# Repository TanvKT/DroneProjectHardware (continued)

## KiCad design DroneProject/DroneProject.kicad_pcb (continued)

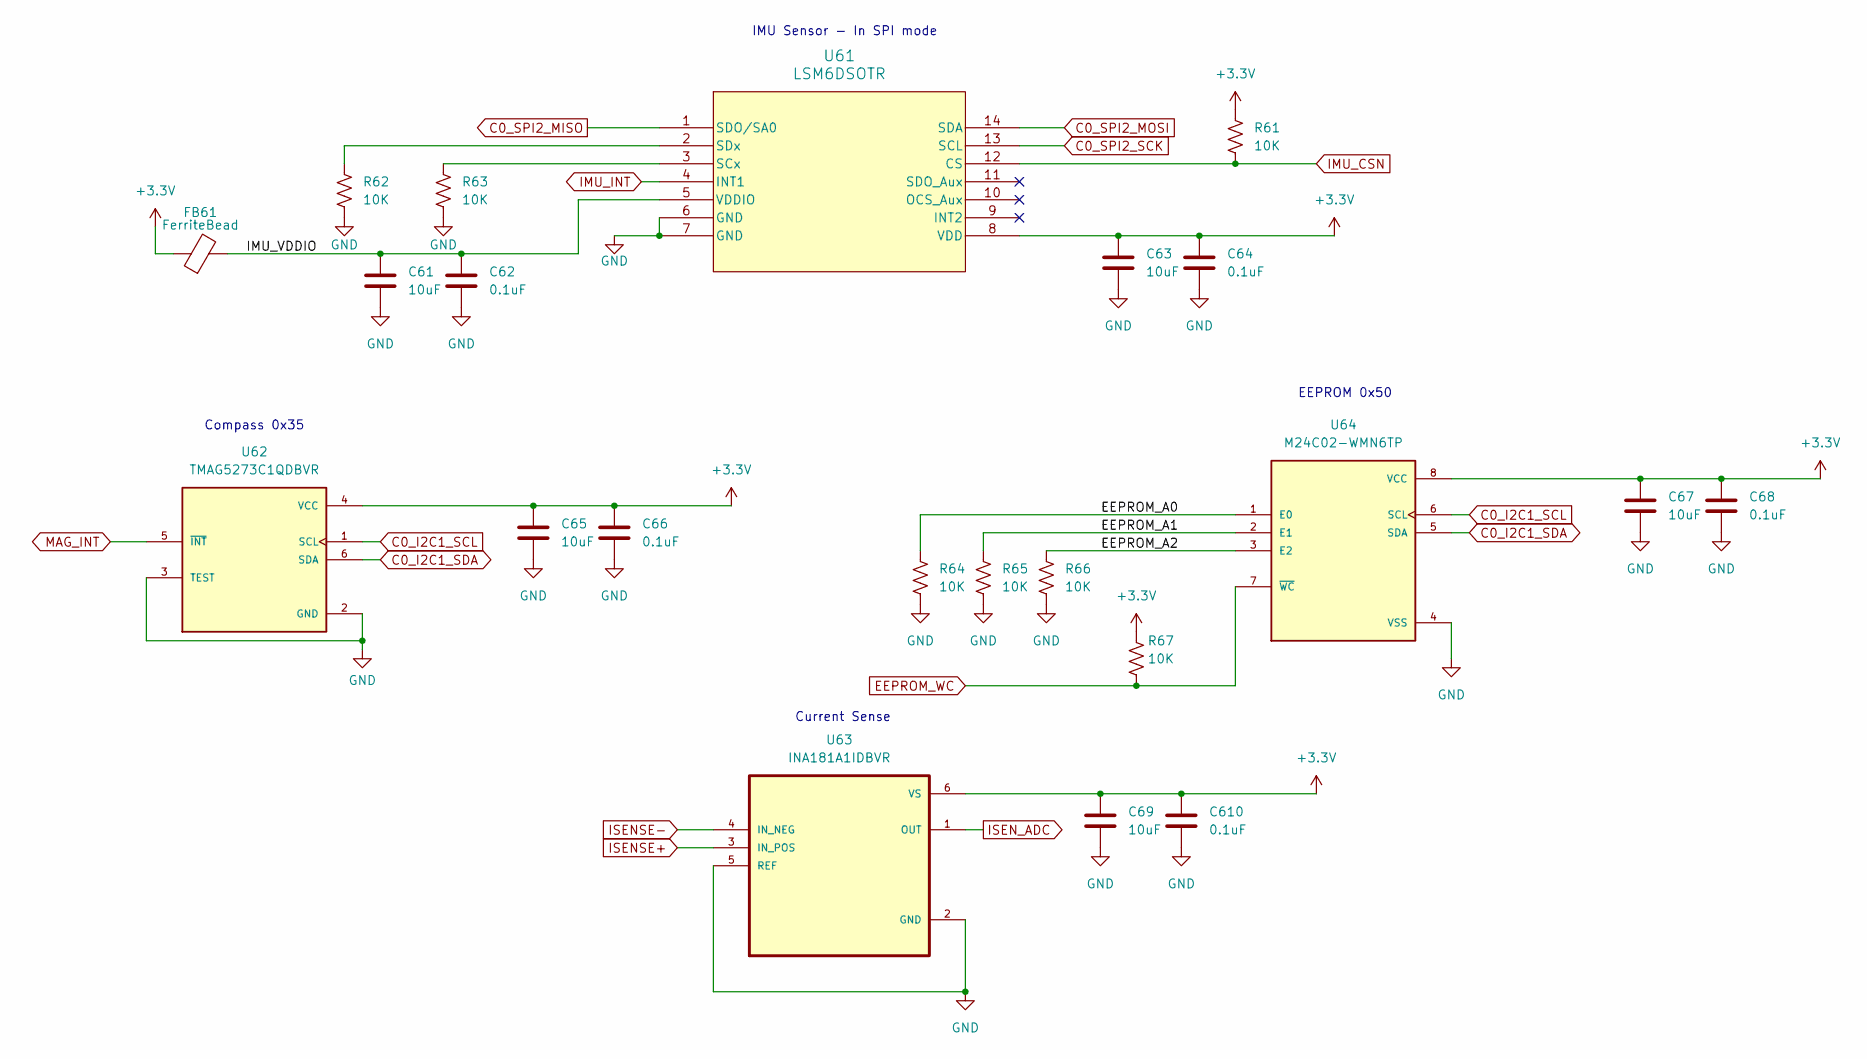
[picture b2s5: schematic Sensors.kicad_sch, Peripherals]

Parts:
C61, C63, C65, C67, C69: 10uF; C_1206_3216Metric
C62, C64, C66, C68, C610: 0.1uF; C_0402_1005Metric
FB61: FerriteBead; L_0805_2012Metric
R61, R62, R63, R64, R65, R66, R67: 10K; R_0402_1005Metric
U61: LSM6DSOTR; LGA-14L_2P5X3X0P86_STM
U62: TMAG5273C1QDBVR; SOT95P280X140-6N; PARTREV B
U63: INA181A1IDBVR; SOT95P280X145-6N
U64: M24C02-WMN6TP; SOIC127P600X175-8N; PARTREV 8

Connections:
+3.3V: C63.1, C64.1, C65.1, C66.1, C67.1, C68.1, C69.1, C610.1, FB61.1, R61.2, R67.2, U61.8 (VDD), U62.4 (VCC), U63.6 (VS), U64.8 (VCC); also elsewhere on the board
/Peripherals/EEPROM_A0: R64.2, U64.1 (E0)
/Peripherals/EEPROM_A1: R65.2, U64.2 (E1)
/Peripherals/EEPROM_A2: R66.2, U64.3 (E2)
/Peripherals/IMU_VDDIO: C61.1, C62.1, FB61.2, U61.5 (VDDIO)
C0_I2C1_SCL: U62.1 (SCL), U64.6 (SCL); also elsewhere on the board
C0_I2C1_SDA: U62.6 (SDA), U64.5 (SDA); also elsewhere on the board
C0_SPI2_MISO: U61.1 (SDO/SA0); also elsewhere on the board
C0_SPI2_MOSI: U61.14 (SDA); also elsewhere on the board
C0_SPI2_SCK: U61.13 (SCL); also elsewhere on the board
EEPROM_WC: R67.1, U64.7 (~WC); also elsewhere on the board
GND: C61.2, C62.2, C63.2, C64.2, C65.2, C66.2, C67.2, C68.2, C69.2, C610.2, R62.1, R63.1, R64.1, R65.1, R66.1, U61.6 (GND), U61.7 (GND), U62.2 (GND), U62.3 (TEST), U63.2 (GND), U63.5 (REF), U64.4 (VSS); also elsewhere on the board
IMU_CSN: R61.1, U61.12 (CS); also elsewhere on the board
IMU_INT: U61.4 (INT1); also elsewhere on the board
ISENSE+: U63.3 (IN_POS); also elsewhere on the board
ISENSE-: U63.4 (IN_NEG); also elsewhere on the board
ISEN_ADC: U63.1 (OUT); also elsewhere on the board
MAG_INT: U62.5 (~INT); also elsewhere on the board
unnamed: R63.2, U61.3 (SCx)
unnamed: R62.2, U61.2 (SDx)

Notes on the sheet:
IMU Sensor - In SPI mode
Compass 0x35
Current Sense
EEPROM 0x50

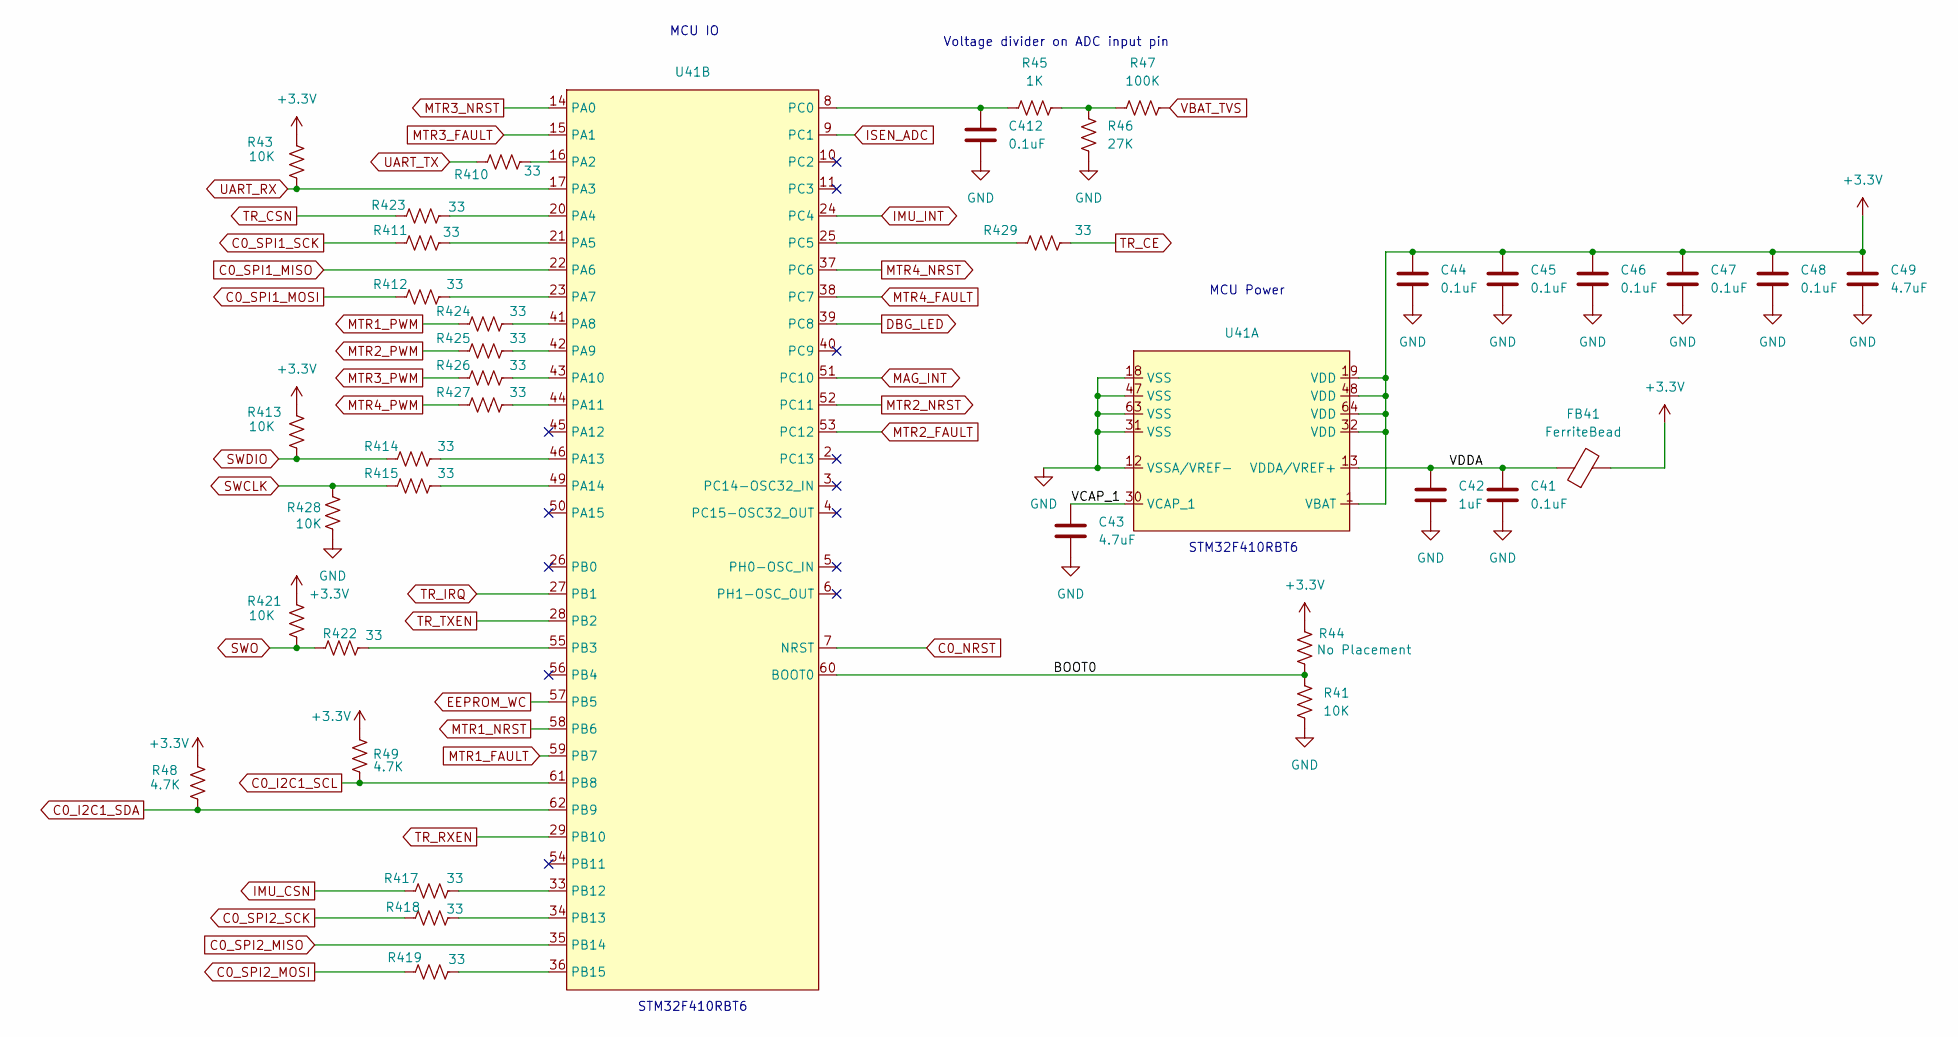
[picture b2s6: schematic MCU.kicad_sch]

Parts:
C41, C44, C45, C46, C47, C48, C412: 0.1uF; C_0402_1005Metric
C42: 1uF; C_0402_1005Metric
C43, C49: 4.7uF; C_0805_2012Metric
FB41: FerriteBead; L_0805_2012Metric
R41, R43, R413, R421, R428: 10K; R_0402_1005Metric
R44: No Placement; R_0402_1005Metric
R45: 1K; R_0402_1005Metric
R46: 27K; R_0402_1005Metric
R47: 100K; R_0402_1005Metric
R48, R49: 4.7K; R_0402_1005Metric
R410, R411, R412, R414, R415, R417, R418, R419, R422, R423, R424, R425, R426, R427, R429: 33; R_0402_1005Metric
U41: STM32F410RBT6; LQFP64-10x10mm

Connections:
+3.3V: C44.1, C45.1, C46.1, C47.1, C48.1, C49.1, FB41.2, R43.2, R44.2, R48.2, R49.2, R413.2, R421.2, U41.1 (VBAT), U41.19 (VDD), U41.32 (VDD), U41.48 (VDD), U41.64 (VDD); also elsewhere on the board
/MCU/BOOT0: R41.2, R44.1, U41.60 (BOOT0)
/MCU/VCAP_1: C43.1, U41.30 (VCAP_1)
/MCU/VDDA: C41.1, C42.1, FB41.1, U41.13 (VDDA/VREF+)
C0_I2C1_SCL: R49.1, U41.61 (PB8); also elsewhere on the board
C0_I2C1_SDA: R48.1, U41.62 (PB9); also elsewhere on the board
C0_NRST: U41.7 (NRST); also elsewhere on the board
C0_SPI1_MISO: U41.22 (PA6); also elsewhere on the board
C0_SPI1_MOSI: R412.1; also elsewhere on the board
C0_SPI1_SCK: R411.1; also elsewhere on the board
C0_SPI2_MISO: U41.35 (PB14); also elsewhere on the board
C0_SPI2_MOSI: R419.1; also elsewhere on the board
C0_SPI2_SCK: R418.1; also elsewhere on the board
DBG_LED: U41.39 (PC8); also elsewhere on the board
EEPROM_WC: U41.57 (PB5); also elsewhere on the board
GND: C41.2, C42.2, C43.2, C44.2, C45.2, C46.2, C47.2, C48.2, C49.2, C412.2, R41.1, R46.1, R428.1, U41.12 (VSSA/VREF-), U41.18 (VSS), U41.31 (VSS), U41.47 (VSS), U41.63 (VSS); also elsewhere on the board
IMU_CSN: R417.1; also elsewhere on the board
IMU_INT: U41.24 (PC4); also elsewhere on the board
ISEN_ADC: U41.9 (PC1); also elsewhere on the board
MAG_INT: U41.51 (PC10); also elsewhere on the board
MTR1_FAULT: U41.59 (PB7); also elsewhere on the board
MTR1_NRST: U41.58 (PB6); also elsewhere on the board
MTR1_PWM: R424.1; also elsewhere on the board
MTR2_FAULT: U41.53 (PC12); also elsewhere on the board
MTR2_NRST: U41.52 (PC11); also elsewhere on the board
MTR2_PWM: R425.1; also elsewhere on the board
MTR3_FAULT: U41.15 (PA1); also elsewhere on the board
MTR3_NRST: U41.14 (PA0); also elsewhere on the board
MTR3_PWM: R426.1; also elsewhere on the board
MTR4_FAULT: U41.38 (PC7); also elsewhere on the board
MTR4_NRST: U41.37 (PC6); also elsewhere on the board
MTR4_PWM: R427.1; also elsewhere on the board
unnamed: R45.2, R46.2, R47.1
unnamed: R410.2, U41.16 (PA2)
unnamed: R423.2, U41.20 (PA4)
unnamed: R411.2, U41.21 (PA5)
unnamed: R412.2, U41.23 (PA7)
unnamed: R424.2, U41.41 (PA8)
unnamed: R425.2, U41.42 (PA9)
unnamed: R426.2, U41.43 (PA10)
unnamed: R427.2, U41.44 (PA11)
unnamed: R414.2, U41.46 (PA13)
unnamed: R415.2, U41.49 (PA14)
unnamed: R422.2, U41.55 (PB3)
unnamed: R417.2, U41.33 (PB12)
unnamed: R418.2, U41.34 (PB13)
unnamed: R419.2, U41.36 (PB15)
unnamed: C412.1, R45.1, U41.8 (PC0)
unnamed: R429.1, U41.25 (PC5)
SWCLK: R415.1, R428.2; also elsewhere on the board
SWDIO: R413.1, R414.1; also elsewhere on the board
SWO: R421.1, R422.1; also elsewhere on the board
TR_CE: R429.2; also elsewhere on the board
TR_CSN: R423.1; also elsewhere on the board
TR_IRQ: U41.27 (PB1); also elsewhere on the board
TR_RXEN: U41.29 (PB10); also elsewhere on the board
TR_TXEN: U41.28 (PB2); also elsewhere on the board
UART_RX: R43.1, U41.17 (PA3); also elsewhere on the board
UART_TX: R410.1; also elsewhere on the board
VBAT_TVS: R47.2; also elsewhere on the board

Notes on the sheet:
Voltage divider on ADC input pin
STM32F410RBT6
MCU Power
MCU IO

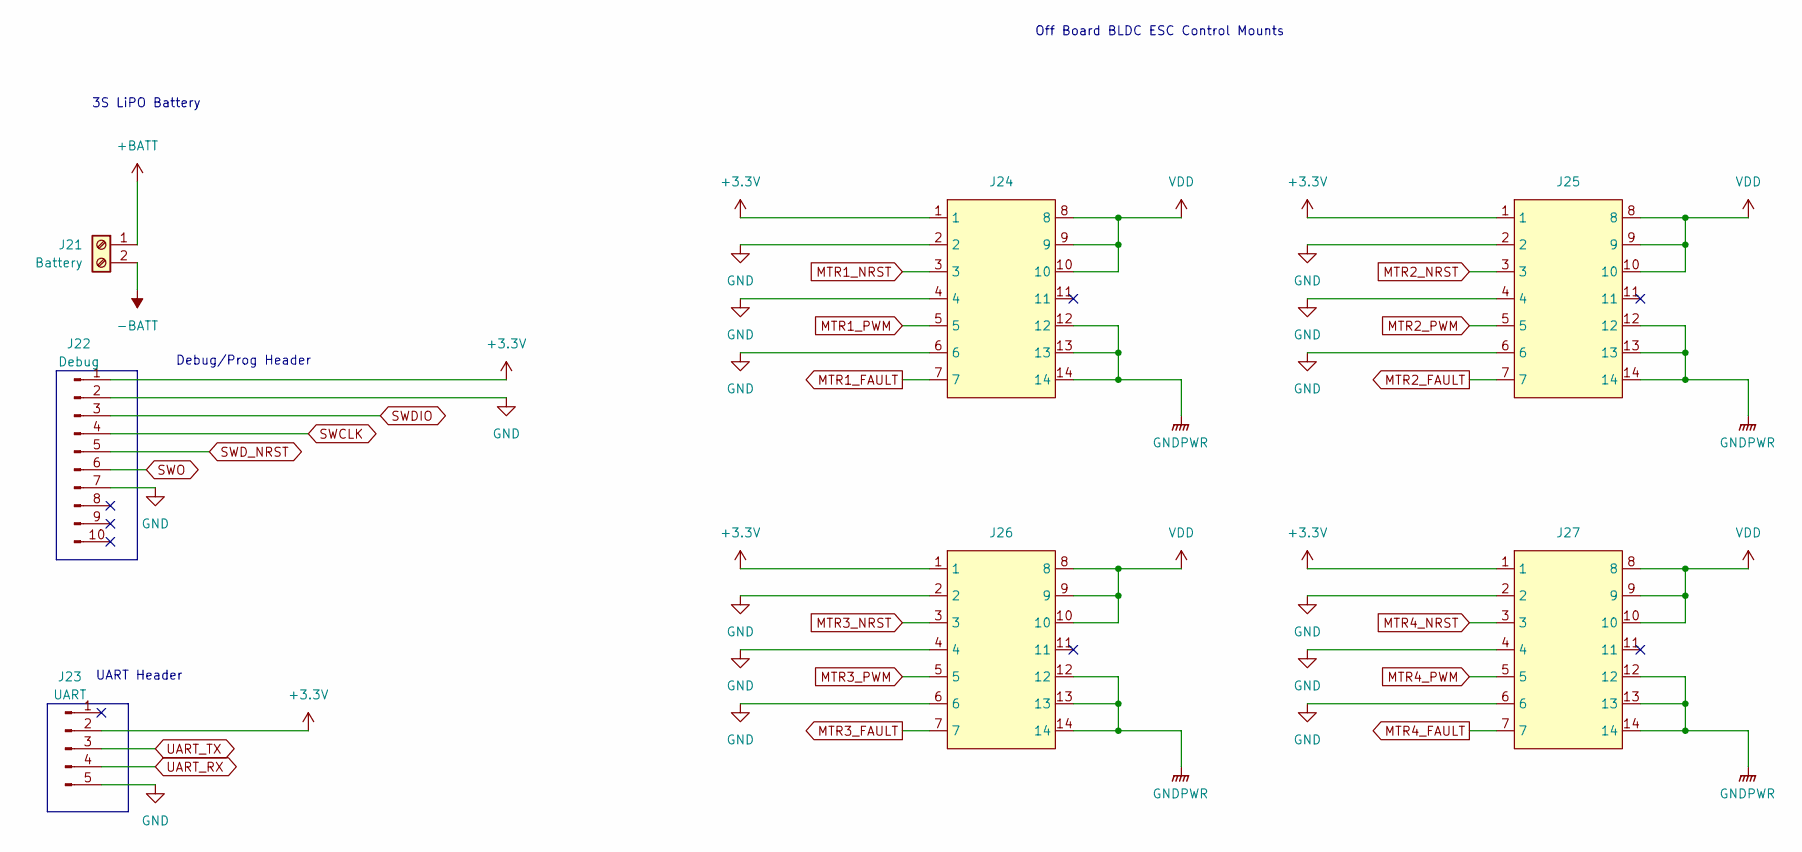
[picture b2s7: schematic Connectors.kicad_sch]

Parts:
J21: Battery; CUI_TB002-500-02BE
J22: Debug; PinHeader_2x05_P2.54mm_Vertical
J23: UART; PinHeader_1x05_P2.54mm_Vertical
J24, J25, J26, J27: BrushlessESC

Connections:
+3.3V: J22.1, J23.2, J24.1, J25.1, J26.1, J27.1; also elsewhere on the board
+BATT: J21.1; also elsewhere on the board
-BATT: J21.2; also elsewhere on the board
GND: J22.2, J22.7, J23.5, J24.2, J24.4, J24.6, J25.2, J25.4, J25.6, J26.2, J26.4, J26.6, J27.2, J27.4, J27.6; also elsewhere on the board
GNDPWR: J24.12, J24.13, J24.14, J25.12, J25.13, J25.14, J26.12, J26.13, J26.14, J27.12, J27.13, J27.14; also elsewhere on the board
MTR1_FAULT: J24.7; also elsewhere on the board
MTR1_NRST: J24.3; also elsewhere on the board
MTR1_PWM: J24.5; also elsewhere on the board
MTR2_FAULT: J25.7; also elsewhere on the board
MTR2_NRST: J25.3; also elsewhere on the board
MTR2_PWM: J25.5; also elsewhere on the board
MTR3_FAULT: J26.7; also elsewhere on the board
MTR3_NRST: J26.3; also elsewhere on the board
MTR3_PWM: J26.5; also elsewhere on the board
MTR4_FAULT: J27.7; also elsewhere on the board
MTR4_NRST: J27.3; also elsewhere on the board
MTR4_PWM: J27.5; also elsewhere on the board
SWCLK: J22.4; also elsewhere on the board
SWDIO: J22.3; also elsewhere on the board
SWD_NRST: J22.5; also elsewhere on the board
SWO: J22.6; also elsewhere on the board
UART_RX: J23.4; also elsewhere on the board
UART_TX: J23.3; also elsewhere on the board
VDD: J24.8, J24.9, J24.10, J25.8, J25.9, J25.10, J26.8, J26.9, J26.10, J27.8, J27.9, J27.10; also elsewhere on the board

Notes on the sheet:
UART Header
Debug/Prog Header
Off Board BLDC ESC Control Mounts
3S LiPO Battery

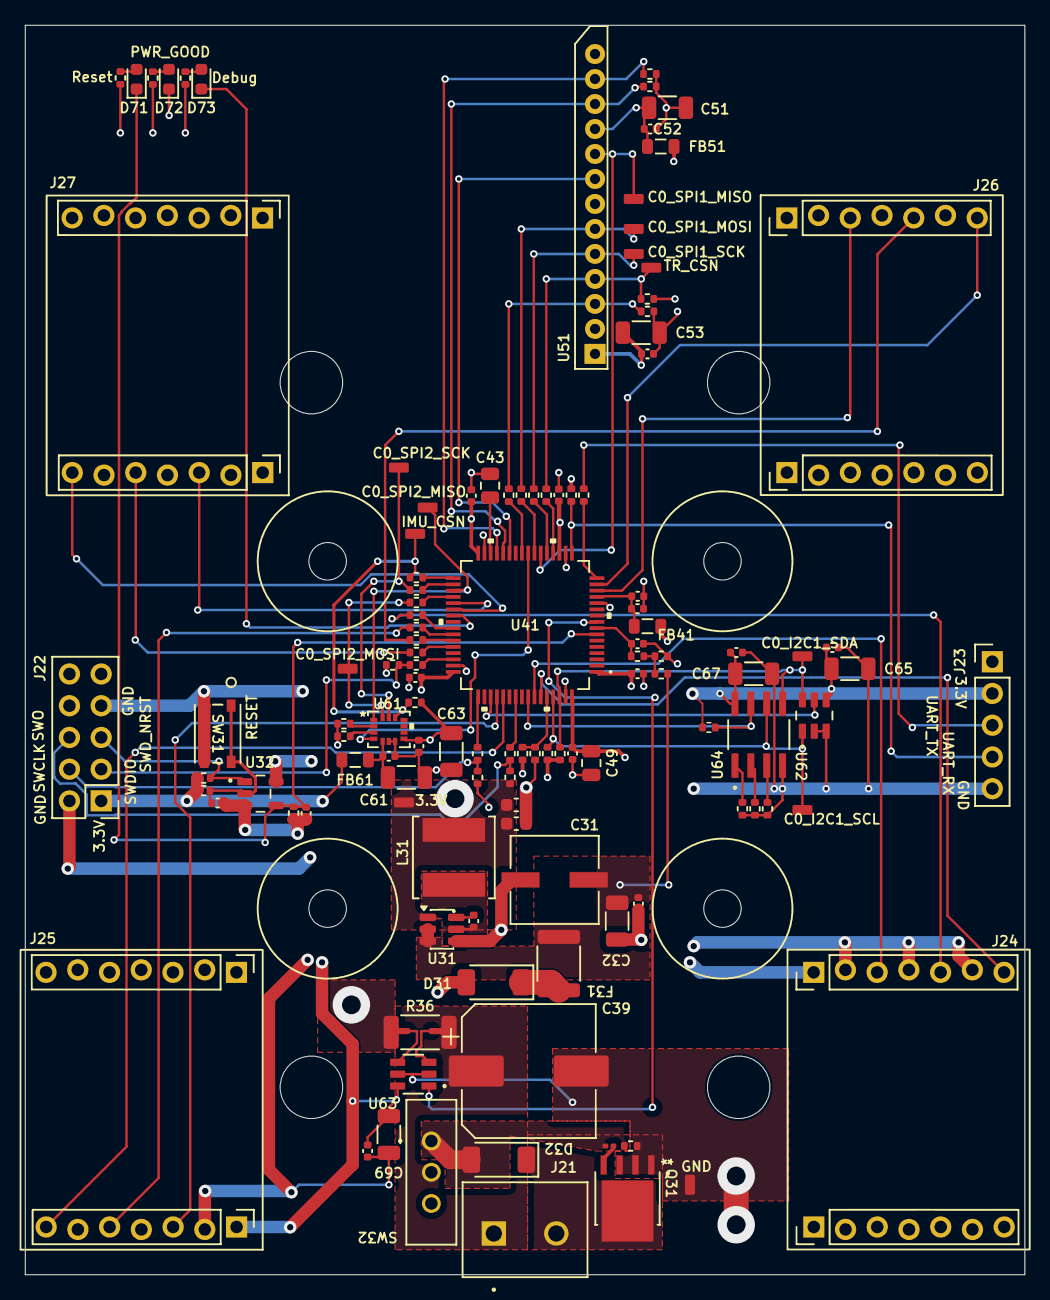
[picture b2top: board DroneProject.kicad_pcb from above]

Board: 4 copper layers, 80.0 x 100.0 mm, 130 parts (0 on the bottom side), 83 nets.

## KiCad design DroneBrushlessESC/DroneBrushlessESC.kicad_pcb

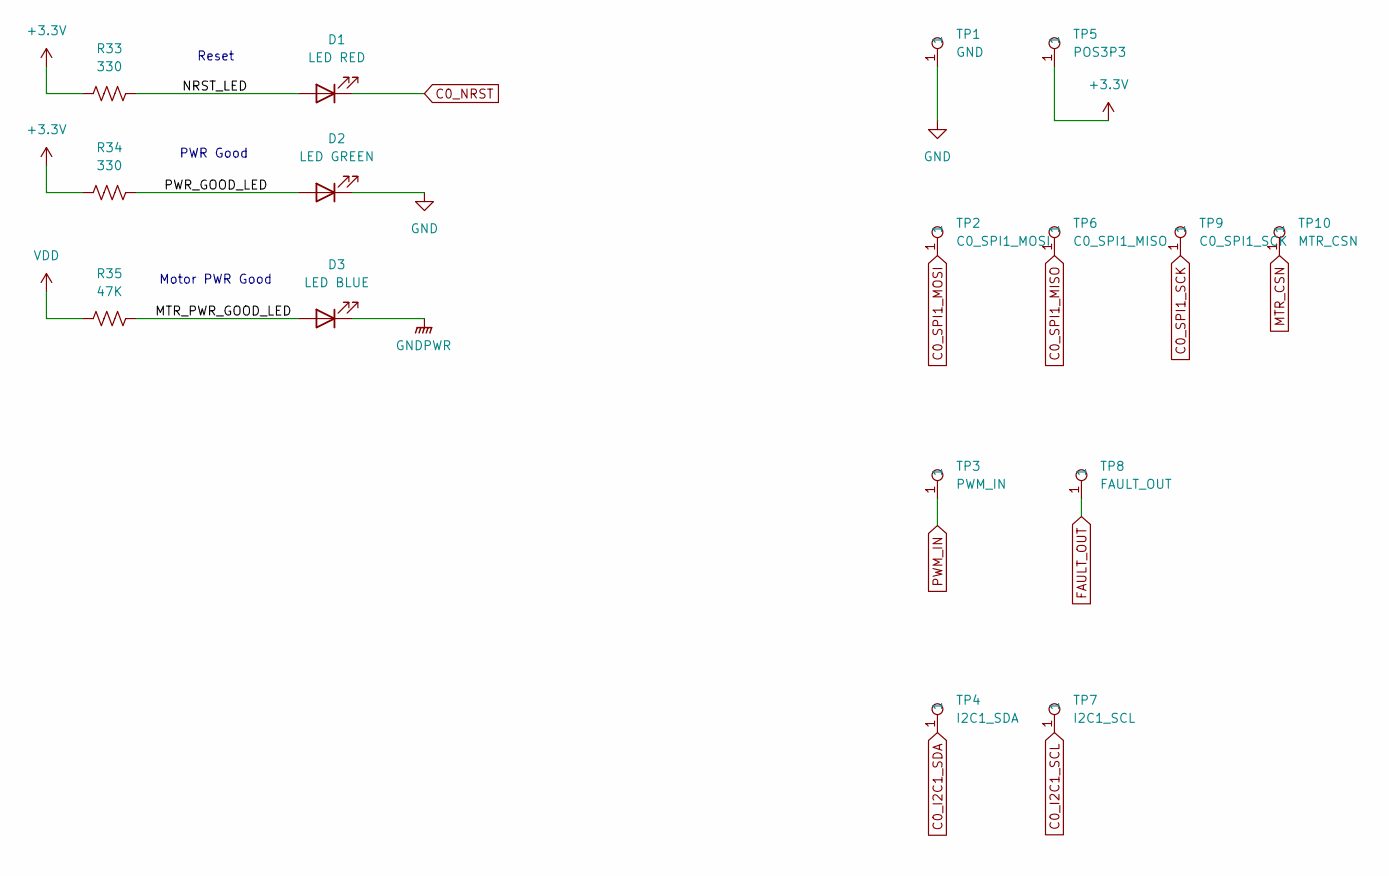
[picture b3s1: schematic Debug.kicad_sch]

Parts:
D1: LED RED; LED_0603_1608Metric
D2: LED GREEN; LED_0603_1608Metric
D3: LED BLUE; LED_0603_1608Metric
R33, R34: 330; R_0402_1005Metric
R35: 47K; R_0402_1005Metric
TP1: GND; Testpoint 1.6mm x 0.8mm
TP2: C0_SPI1_MOSI; Testpoint 1.6mm x 0.8mm
TP3: PWM_IN; Testpoint 1.6mm x 0.8mm
TP4: I2C1_SDA; Testpoint 1.6mm x 0.8mm
TP5: POS3P3; Testpoint 1.6mm x 0.8mm
TP6: C0_SPI1_MISO; Testpoint 1.6mm x 0.8mm
TP7: I2C1_SCL; Testpoint 1.6mm x 0.8mm
TP8: FAULT_OUT; Testpoint 1.6mm x 0.8mm
TP9: C0_SPI1_SCK; Testpoint 1.6mm x 0.8mm
TP10: MTR_CSN; Testpoint 1.6mm x 0.8mm

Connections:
+3.3V: R33.1, R34.1, TP5.1; also elsewhere on the board
/Debug/MTR_PWR_GOOD_LED: D3.2 (A), R35.2
/Debug/NRST_LED: D1.2 (A), R33.2
/Debug/PWR_GOOD_LED: D2.2 (A), R34.2
C0_I2C1_SCL: TP7.1; also elsewhere on the board
C0_I2C1_SDA: TP4.1; also elsewhere on the board
C0_NRST: D1.1 (K); also elsewhere on the board
C0_SPI1_MISO: TP6.1; also elsewhere on the board
C0_SPI1_MOSI: TP2.1; also elsewhere on the board
C0_SPI1_SCK: TP9.1; also elsewhere on the board
FAULT_OUT: TP8.1; also elsewhere on the board
GND: D2.1 (K), TP1.1; also elsewhere on the board
GNDPWR: D3.1 (K); also elsewhere on the board
MTR_CSN: TP10.1; also elsewhere on the board
PWM_IN: TP3.1; also elsewhere on the board
VDD: R35.1; also elsewhere on the board

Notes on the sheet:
Reset
PWR Good
Motor PWR Good

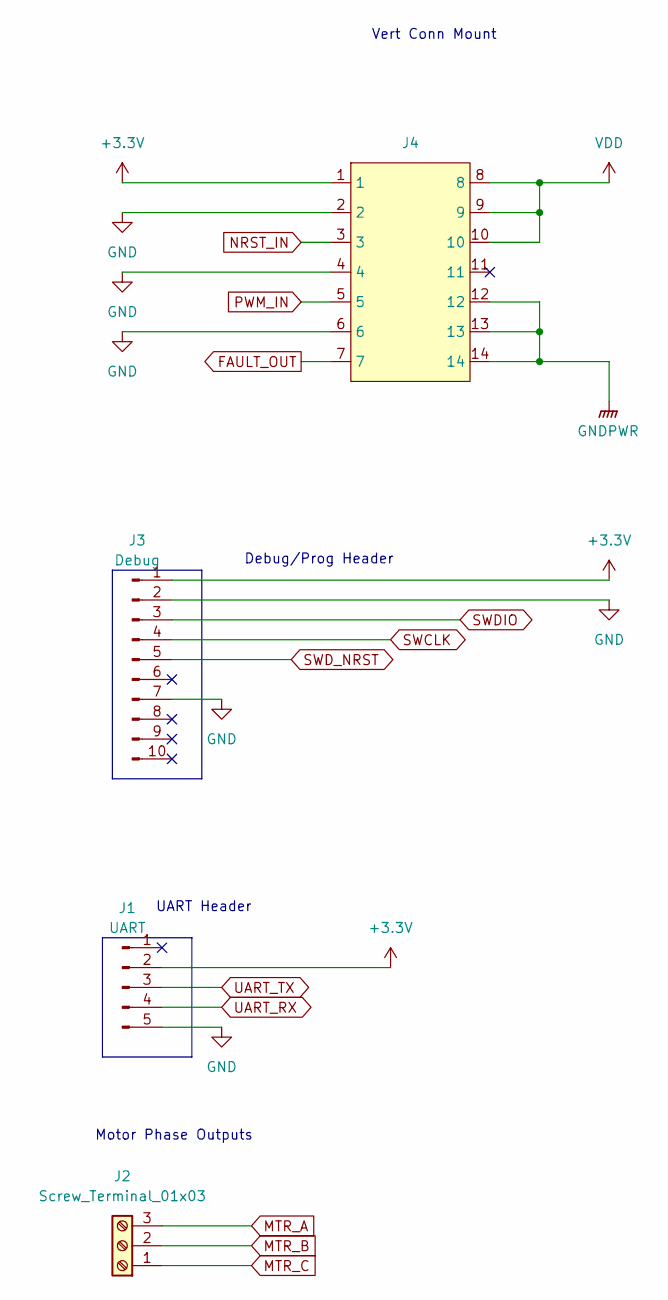
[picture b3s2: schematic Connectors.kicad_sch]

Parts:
J1: UART; PinHeader_1x05_P2.54mm_Vertical
J2: Screw_Terminal_01x03; CUI_TB005_-762-03BE
J3: Debug; PinHeader_2x05_P2.54mm_Vertical
J4: BrushlessESC

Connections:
+3.3V: J1.2, J3.1, J4.1; also elsewhere on the board
FAULT_OUT: J4.7; also elsewhere on the board
GND: J1.5, J3.2, J3.7, J4.2, J4.4, J4.6; also elsewhere on the board
GNDPWR: J4.12, J4.13, J4.14; also elsewhere on the board
MTR_A: J2.3; also elsewhere on the board
MTR_B: J2.2; also elsewhere on the board
MTR_C: J2.1; also elsewhere on the board
NRST_IN: J4.3; also elsewhere on the board
PWM_IN: J4.5; also elsewhere on the board
SWCLK: J3.4; also elsewhere on the board
SWDIO: J3.3; also elsewhere on the board
SWD_NRST: J3.5; also elsewhere on the board
UART_RX: J1.4; also elsewhere on the board
UART_TX: J1.3; also elsewhere on the board
VDD: J4.8, J4.9, J4.10; also elsewhere on the board

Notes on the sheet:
Motor Phase Outputs
UART Header
Debug/Prog Header
Vert Conn Mount

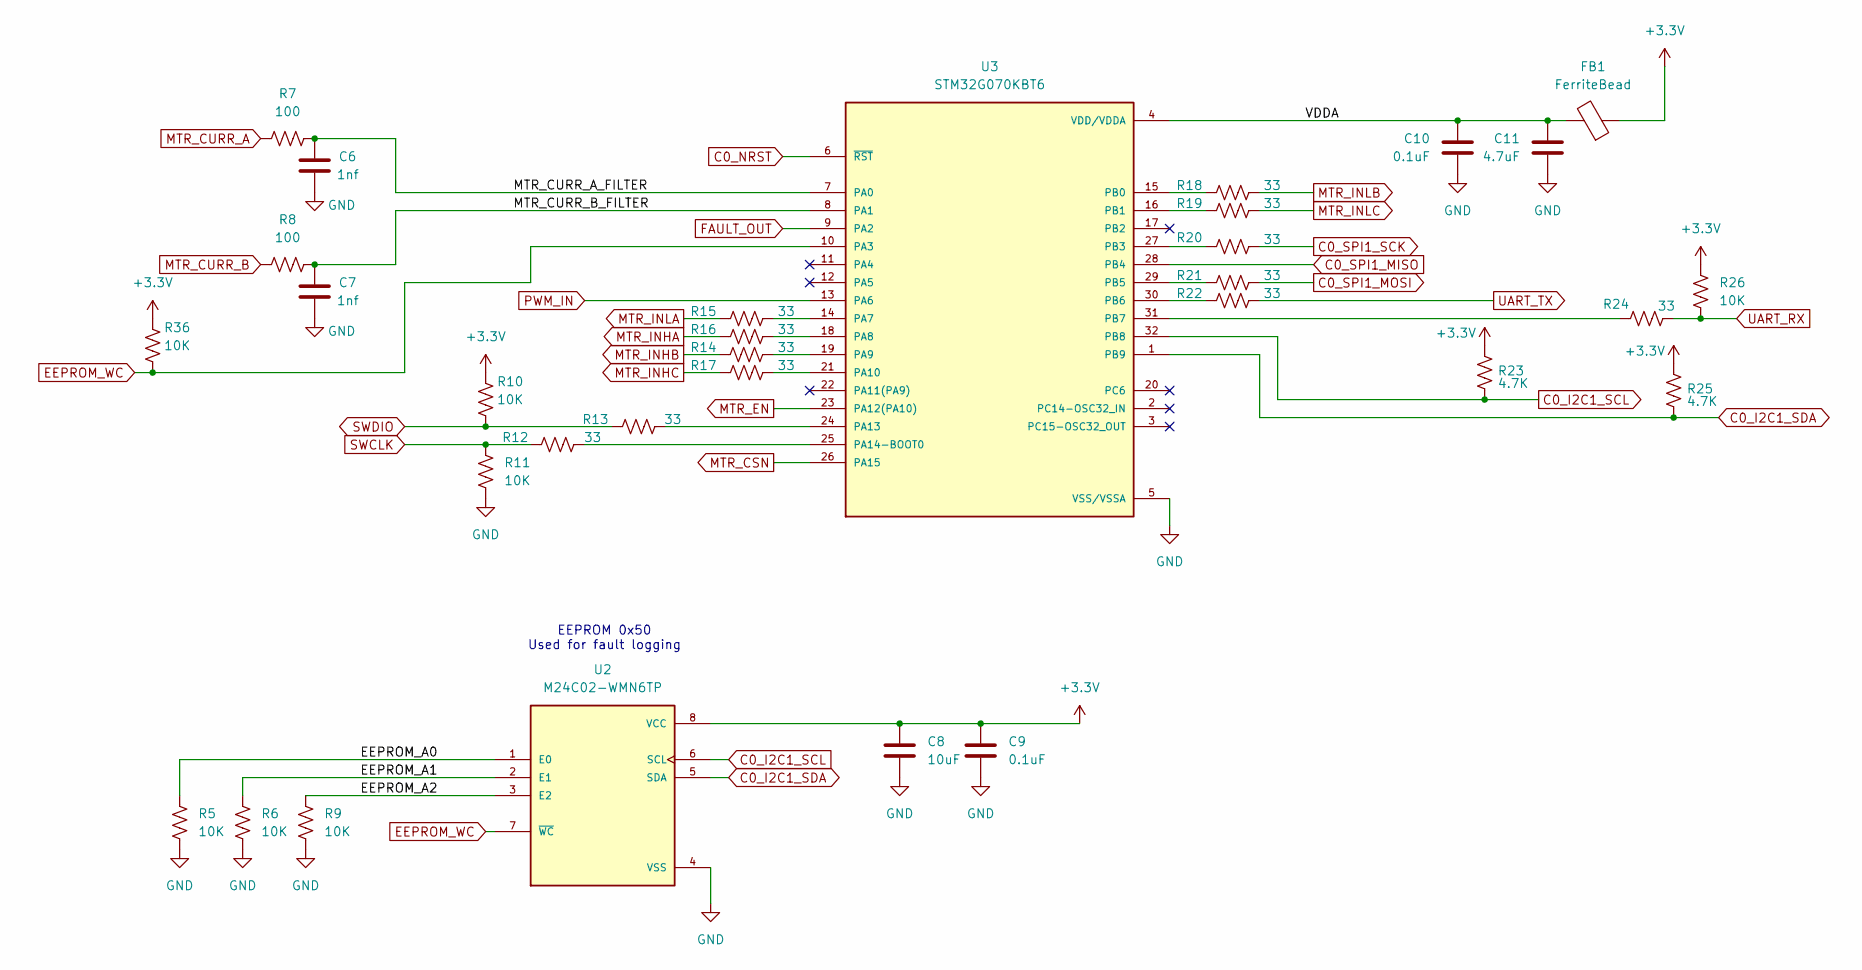
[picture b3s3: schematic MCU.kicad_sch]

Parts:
C6, C7: 1nf; C_0402_1005Metric
C8: 10uF; C_1206_3216Metric
C9, C10: 0.1uF; C_0402_1005Metric
C11: 4.7uF; C_0805_2012Metric
FB1: FerriteBead; L_0805_2012Metric
R5, R6, R9, R10, R11, R26, R36: 10K; R_0402_1005Metric
R7, R8: 100; R_0402_1005Metric
R12, R13, R14, R15, R16, R17, R18, R19, R20, R21, R22, R24: 33; R_0402_1005Metric
R23, R25: 4.7K; R_0402_1005Metric
U2: M24C02-WMN6TP; SOIC127P600X175-8N; PARTREV 8
U3: STM32G070KBT6; QFP80P900X900X160-32N; PARTREV 2

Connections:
+3.3V: C8.1, C9.1, FB1.1, R10.2, R23.2, R25.2, R26.2, R36.2, U2.8 (VCC); also elsewhere on the board
/MCU/EEPROM_A0: R5.2, U2.1 (E0)
/MCU/EEPROM_A1: R6.2, U2.2 (E1)
/MCU/EEPROM_A2: R9.2, U2.3 (E2)
/MCU/MTR_CURR_A_FILTER: C6.1, R7.2, U3.7 (PA0)
/MCU/MTR_CURR_B_FILTER: C7.1, R8.2, U3.8 (PA1)
/MCU/VDDA: C10.1, C11.1, FB1.2, U3.4 (VDD/VDDA)
C0_I2C1_SCL: R23.1, U2.6 (SCL), U3.32 (PB8); also elsewhere on the board
C0_I2C1_SDA: R25.1, U2.5 (SDA), U3.1 (PB9); also elsewhere on the board
C0_NRST: U3.6 (~RST); also elsewhere on the board
C0_SPI1_MISO: U3.28 (PB4); also elsewhere on the board
C0_SPI1_MOSI: R21.2; also elsewhere on the board
C0_SPI1_SCK: R20.2; also elsewhere on the board
EEPROM_WC: R36.1, U2.7 (~WC), U3.10 (PA3)
FAULT_OUT: U3.9 (PA2); also elsewhere on the board
GND: C6.2, C7.2, C8.2, C9.2, C10.2, C11.2, R5.1, R6.1, R9.1, R11.1, U2.4 (VSS), U3.5 (VSS/VSSA); also elsewhere on the board
MTR_CSN: U3.26 (PA15); also elsewhere on the board
MTR_CURR_A: R7.1; also elsewhere on the board
MTR_CURR_B: R8.1; also elsewhere on the board
MTR_EN: U3.23 (PA12(PA10)); also elsewhere on the board
MTR_INHA: R16.1; also elsewhere on the board
MTR_INHB: R14.1; also elsewhere on the board
MTR_INHC: R17.1; also elsewhere on the board
MTR_INLA: R15.1; also elsewhere on the board
MTR_INLB: R18.2; also elsewhere on the board
MTR_INLC: R19.2; also elsewhere on the board
unnamed: R15.2, U3.14 (PA7)
unnamed: R16.2, U3.18 (PA8)
unnamed: R14.2, U3.19 (PA9)
unnamed: R17.2, U3.21 (PA10)
unnamed: R13.2, U3.24 (PA13)
unnamed: R12.2, U3.25 (PA14-BOOT0)
unnamed: R18.1, U3.15 (PB0)
unnamed: R19.1, U3.16 (PB1)
unnamed: R20.1, U3.27 (PB3)
unnamed: R21.1, U3.29 (PB5)
unnamed: R22.1, U3.30 (PB6)
unnamed: R24.1, U3.31 (PB7)
PWM_IN: U3.13 (PA6); also elsewhere on the board
SWCLK: R11.2, R12.1; also elsewhere on the board
SWDIO: R10.1, R13.1; also elsewhere on the board
UART_RX: R24.2, R26.1; also elsewhere on the board
UART_TX: R22.2; also elsewhere on the board

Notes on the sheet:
EEPROM 0x50 Used for fault logging

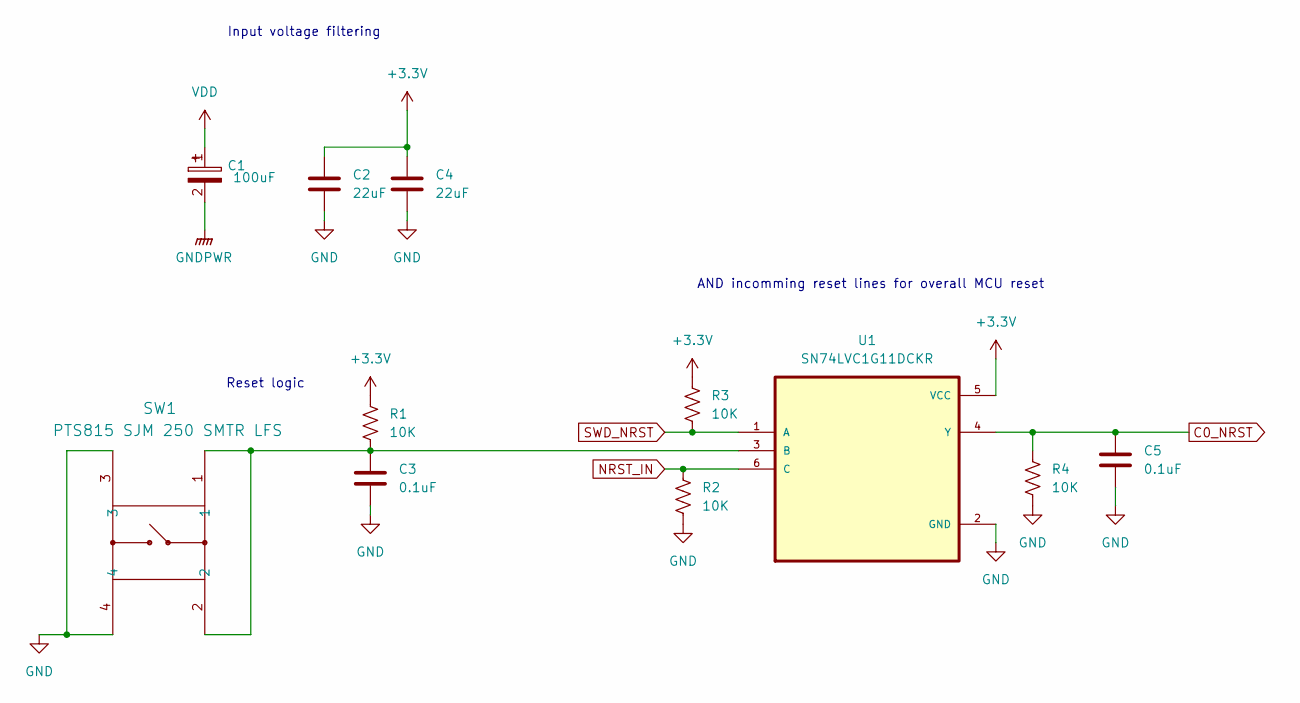
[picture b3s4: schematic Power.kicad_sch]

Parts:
C1: 100uF; CAP_A768EB_6.8x6.8_KEM
C2, C4: 22uF; C_0603_1608Metric
C3, C5: 0.1uF; C_0402_1005Metric
R1, R2, R3, R4: 10K; R_0402_1005Metric
SW1: PTS815 SJM 250 SMTR LFS; SW4_PTS815 SJM 250 SMTR LFS_CNK
U1: SN74LVC1G11DCKR; SOT65P210X110-6N

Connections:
+3.3V: C2.1, C4.1, R1.2, R3.2, U1.5 (VCC); also elsewhere on the board
C0_NRST: C5.1, R4.2, U1.4 (Y); also elsewhere on the board
GND: C2.2, C3.2, C4.2, C5.2, R2.1, R4.1, SW1.3, SW1.4, U1.2 (GND); also elsewhere on the board
GNDPWR: C1.2; also elsewhere on the board
NRST_IN: R2.2, U1.6 (C); also elsewhere on the board
unnamed: C3.1, R1.1, SW1.1, SW1.2, U1.3 (B)
SWD_NRST: R3.1, U1.1 (A); also elsewhere on the board
VDD: C1.1; also elsewhere on the board

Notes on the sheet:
AND incomming reset lines for overall MCU reset
Input voltage filtering
Reset logic
